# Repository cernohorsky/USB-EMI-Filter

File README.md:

# USB-EMI-Filter
USB 2.0 EMC Stick with integrated EMI Filter. Prepared for RTL-SDR dongle and 5V LNA

# To-Do
-L2 footprint has no pads

Voltage ripple measurement

Blue input voltage ripple. Yellow output voltage ripple.

#usb, #filter, #emi, #5v

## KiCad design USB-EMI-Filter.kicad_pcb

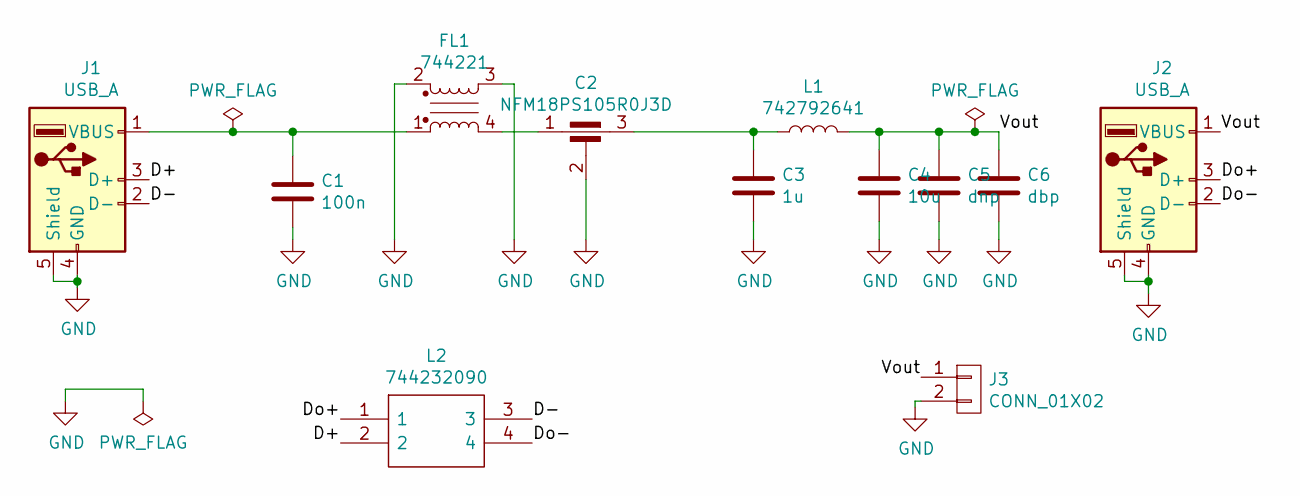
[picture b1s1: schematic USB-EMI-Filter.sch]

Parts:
C1: 100n; C_0603
C2: NFM18PS105R0J3D; C_0603-3Terminal
C3: 1u; C_0603
C4: 10u; C_0805
C5: dnp; C_0805
C6: dbp; C_0805
FL1: 744221; L_CommonMode_Wuerth_WE-SL2
J1: USB_A; USB_A-Male
J2: USB_A
J3: CONN_01X02; Pin_Header_Straight_1x02_Pitch2.54mm
L1: 742792641; C_0603
L2: 744232090; Mouser Part Number 710-744232090

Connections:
/D+: J1.3 (D+), L2.2
/D-: J1.2 (D-), L2.3
/Do+: J2.3 (D+), L2.1
/Do-: J2.2 (D-), L2.4
/Vout: C4.1, C5.1, C6.1, J2.1 (VBUS), J3.1, L1.2
GND: C1.2, C2.2, C3.2, C4.2, C5.2, C6.2, FL1.2, FL1.3, J1.4 (GND), J1.5 (Shield), J2.4 (GND), J2.5 (Shield), J3.2
unnamed: C1.1, FL1.1, J1.1 (VBUS)
unnamed: C2.1, FL1.4
unnamed: C2.3, C3.1, L1.1

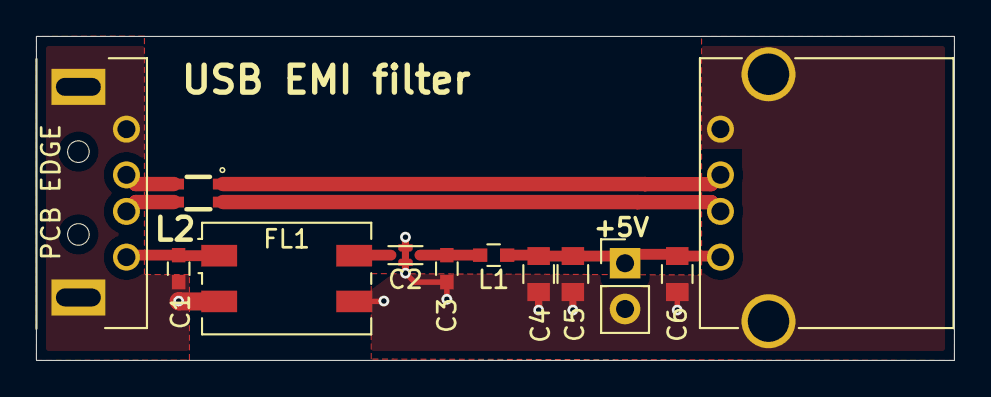
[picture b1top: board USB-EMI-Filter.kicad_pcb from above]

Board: 2 copper layers, 51.0 x 18.0 mm, 12 parts (0 on the bottom side), 9 nets.

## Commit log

2019-04-07 Changed schematic, changed layout
2019-04-08 DRC, ERC passed
2019-04-24 Added gerber files, changed readme
2019-05-10 Manufactured
2019-05-28 Added pictures
2019-05-28 Added speed test results
2019-06-17 Added spectrum measurement
